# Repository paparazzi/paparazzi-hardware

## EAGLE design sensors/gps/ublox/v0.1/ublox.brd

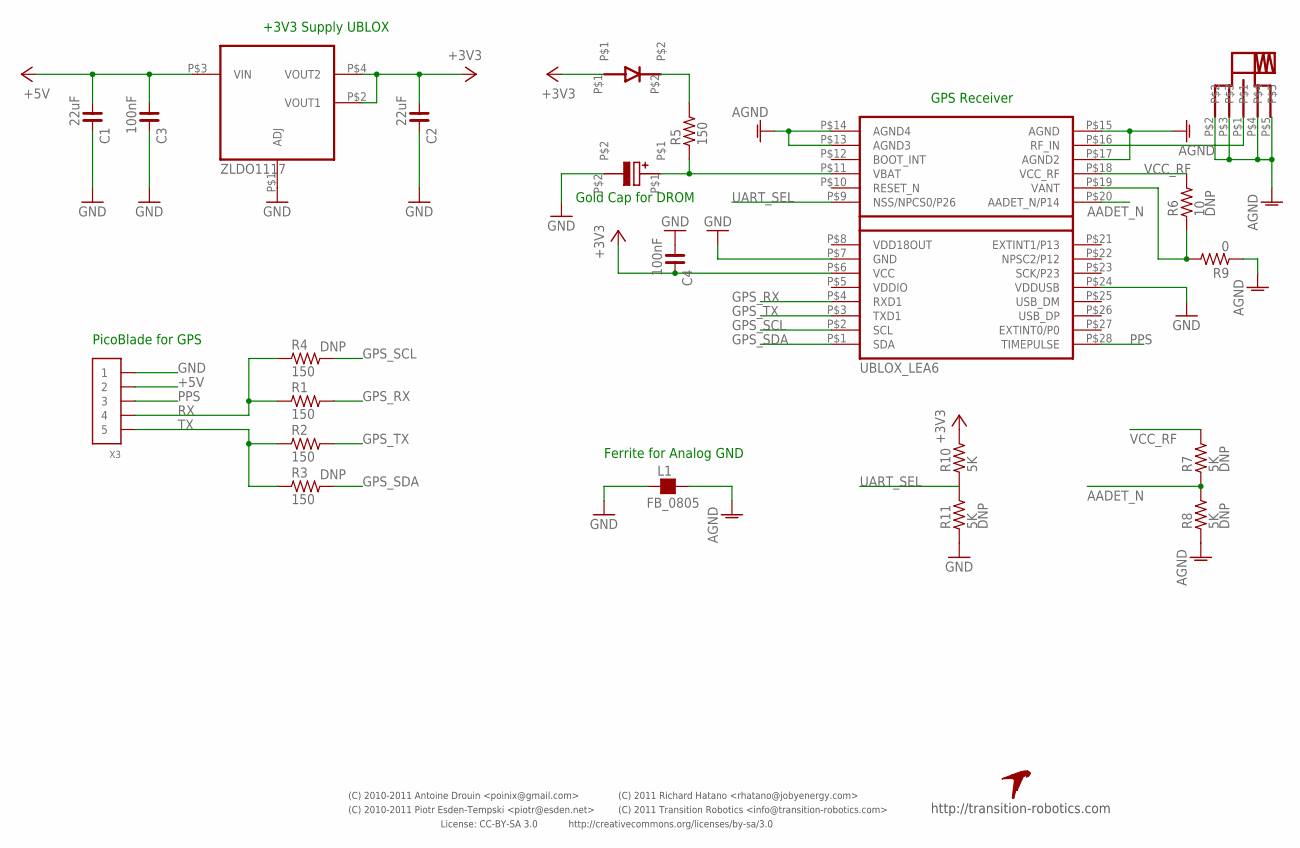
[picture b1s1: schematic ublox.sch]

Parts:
C1, C2: 22uF; C0805
C3, C4: 100nF; C0805
C5: EECEN0F204AK
D1: SOD123
J1: SMA
L1: FB_0805; L0805
R1, R2, R3, R4, R5: 150; R0603
R6: 10; R0603
R7, R8, R10, R11: 5K; R0603
R9: 0; R0603
U1: ZLDO1117
U2: UBLOX_LEA6
U$1: TR-LOGO; PARTNO *
X3: CONN_5-1-53261; PB-53261-05

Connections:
+3V3: C2.1, C4.2, D1.P$1, R10.2, U1.P$2 (VOUT1), U1.P$4 (VOUT2), U2.P$6 (VCC)
+5V: C1.1, C3.1, U1.P$3 (VIN), X3.2
AADET_N: R7.1, R8.2, U2.P$20 (AADET_N/P14)
AGND: J1.P$2, J1.P$3, J1.P$4, J1.P$5, L1.2, R8.1, R9.1, U2.P$13 (AGND3), U2.P$14 (AGND4), U2.P$15 (AGND), U2.P$17 (AGND2)
GND: C1.2, C2.2, C3.2, C4.1, C5.P$2, L1.1, R11.1, U1.P$1 (ADJ), U2.P$7 (GND), U2.P$24 (VDDUSB), X3.1
GPS_RX: R1.2, U2.P$4 (RXD1)
GPS_SCL: R4.2, U2.P$2 (SCL)
GPS_SDA: R3.2, U2.P$1 (SDA)
GPS_TX: R2.2, U2.P$3 (TXD1)
unnamed: R10.1, R11.2
unnamed: D1.P$2, R5.2
unnamed: C5.P$1, R5.1, U2.P$11 (VBAT)
unnamed: J1.P$1, U2.P$16 (RF_IN)
unnamed: R6.1, R9.2, U2.P$19 (VANT)
PPS: U2.P$28 (TIMEPULSE), X3.3
RX: R1.1, R4.1, X3.4
TX: R2.1, R3.1, X3.5
UART_SEL: U2.P$9 (NSS/NPCS0/P26)
VCC_RF: R6.2, R7.2, U2.P$18 (VCC_RF)

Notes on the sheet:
Ferrite for Analog GND
GPS Receiver
PicoBlade for GPS
+3V3 Supply UBLOX
Gold Cap for DROM
License: CC-BY-SA 3.0
http://creativecommons.org/licenses/by-sa/3.0
(C) 2010-2011 Piotr Esden-Tempski <piotr@esden.net>
(C) 2010-2011 Antoine Drouin <poinix@gmail.com>
(C) 2011 Richard Hatano <rhatano@jobyenergy.com>
http://transition-robotics.com
(C) 2011 Transition Robotics <info@transition-robotics.com>

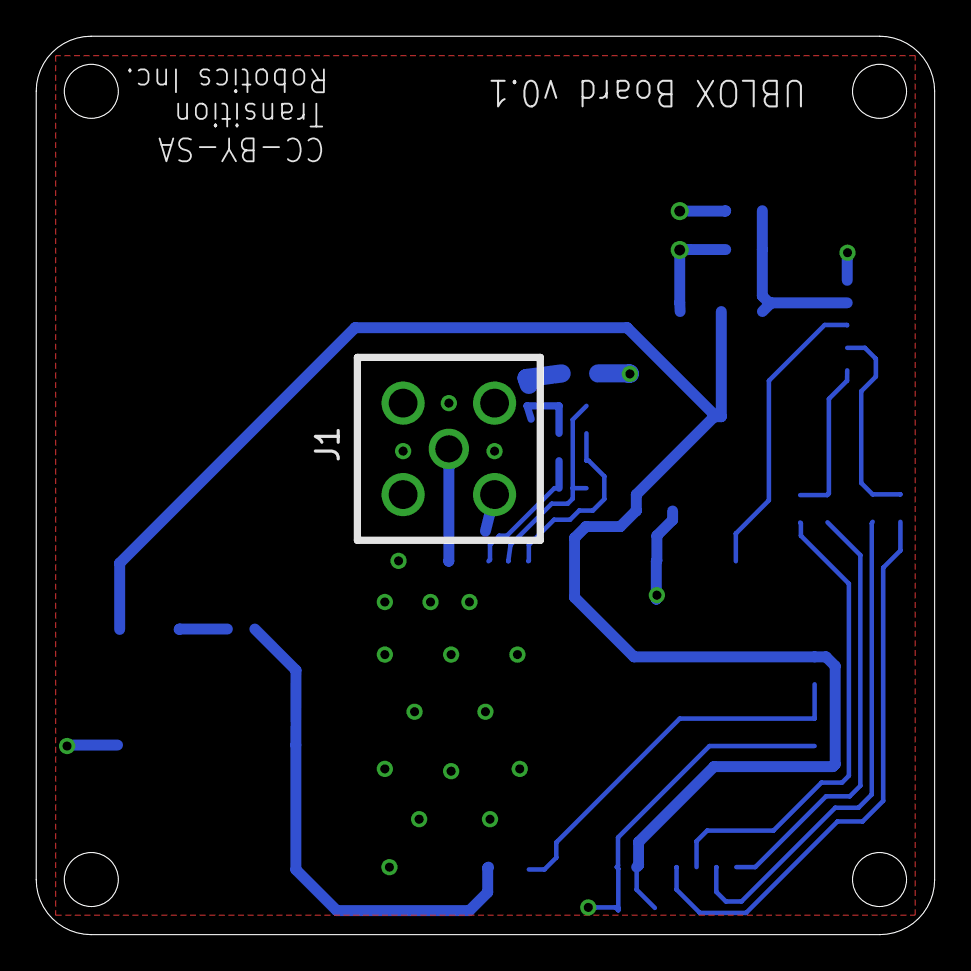
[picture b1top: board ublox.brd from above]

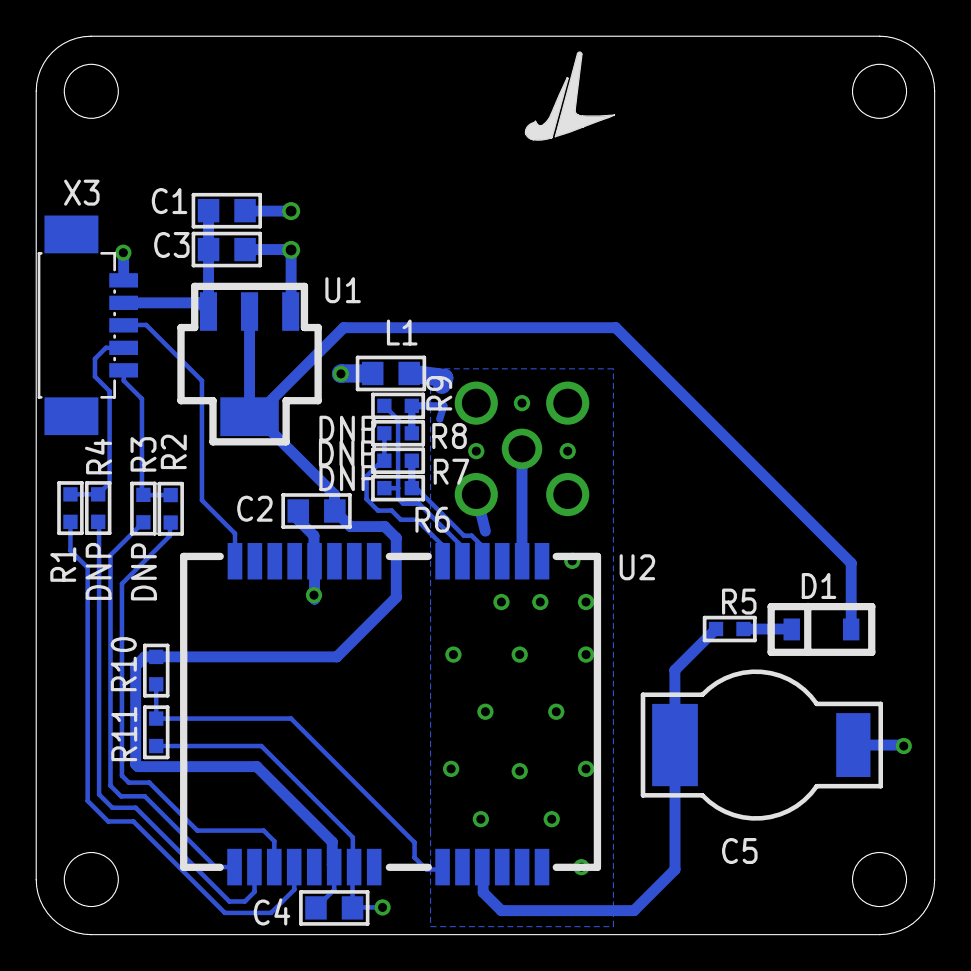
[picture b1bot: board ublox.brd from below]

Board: 4 copper layers, 49.9 x 49.9 mm, 23 parts (22 on the bottom side), 18 nets.

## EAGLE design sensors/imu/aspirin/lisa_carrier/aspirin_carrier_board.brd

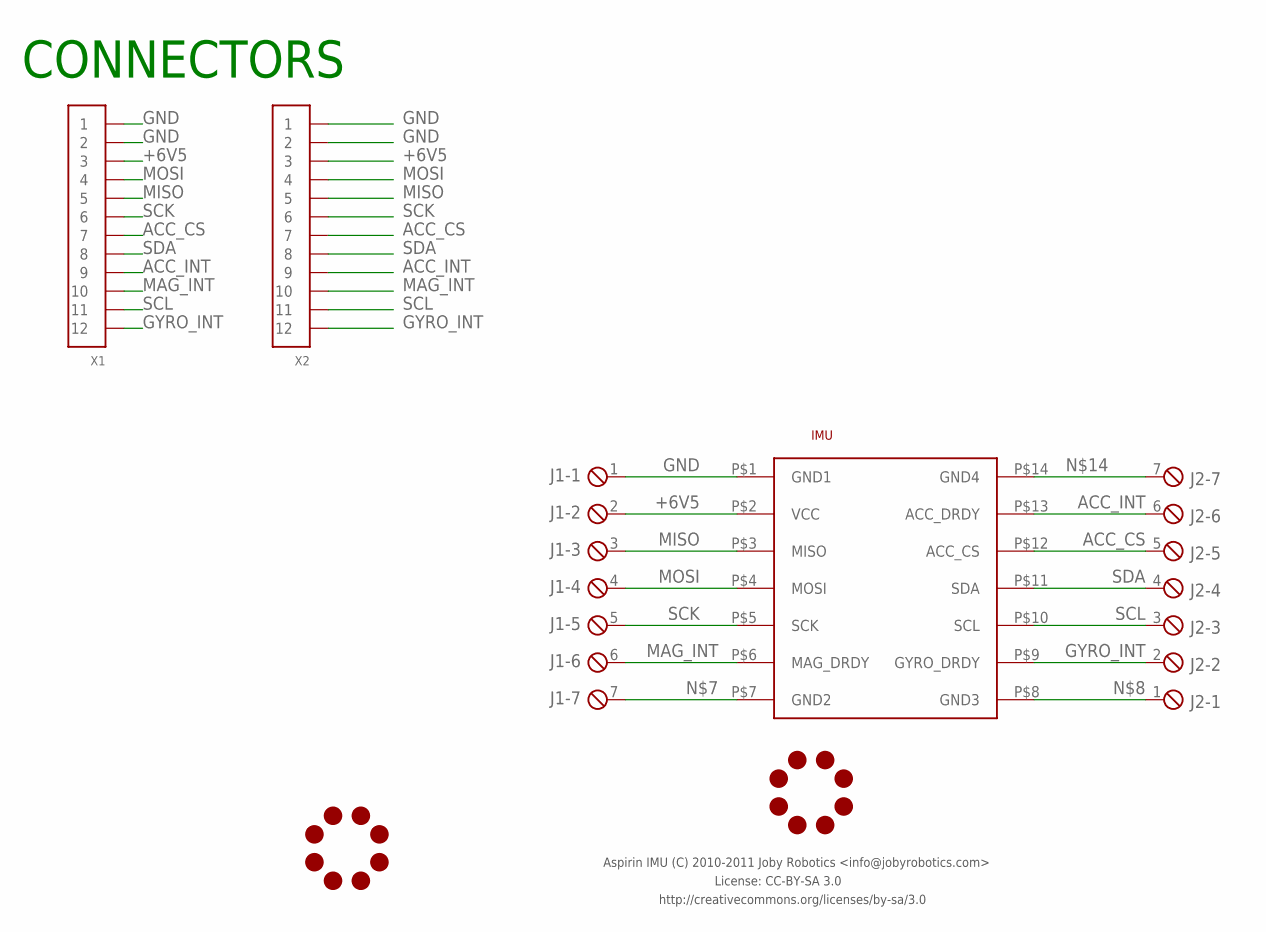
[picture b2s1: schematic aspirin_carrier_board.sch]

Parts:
IMU: ASPIRIN; ASPIRIN_1
J1, J2: MPT7; 7POL254
JL1, JL2: JOBY_LOGO-6MIL; JOBY_LOGO_6MIL
X1: CONN_12-1-53047; PB-53047-12
X2: CONN_12-1-53261; PB-53261-12

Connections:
+6V5: IMU.P$2 (VCC), J1.2, X1.3, X2.3
ACC_CS: IMU.P$12 (ACC_CS), J2.5, X1.7, X2.7
ACC_INT: IMU.P$13 (ACC_DRDY), J2.6, X1.9, X2.9
GND: IMU.P$1 (GND1), J1.1, X1.1, X1.2, X2.1, X2.2
GYRO_INT: IMU.P$9 (GYRO_DRDY), J2.2, X1.12, X2.12
MAG_INT: IMU.P$6 (MAG_DRDY), J1.6, X1.10, X2.10
MISO: IMU.P$3 (MISO), J1.3, X1.5, X2.5
MOSI: IMU.P$4 (MOSI), J1.4, X1.4, X2.4
unnamed: IMU.P$7 (GND2), J1.7
unnamed: IMU.P$8 (GND3), J2.1
unnamed: IMU.P$14 (GND4), J2.7
SCK: IMU.P$5 (SCK), J1.5, X1.6, X2.6
SCL: IMU.P$10 (SCL), J2.3, X1.11, X2.11
SDA: IMU.P$11 (SDA), J2.4, X1.8, X2.8

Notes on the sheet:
CONNECTORS
License: CC-BY-SA 3.0
http://creativecommons.org/licenses/by-sa/3.0
Aspirin IMU (C) 2010-2011 Joby Robotics <info@jobyrobotics.com>

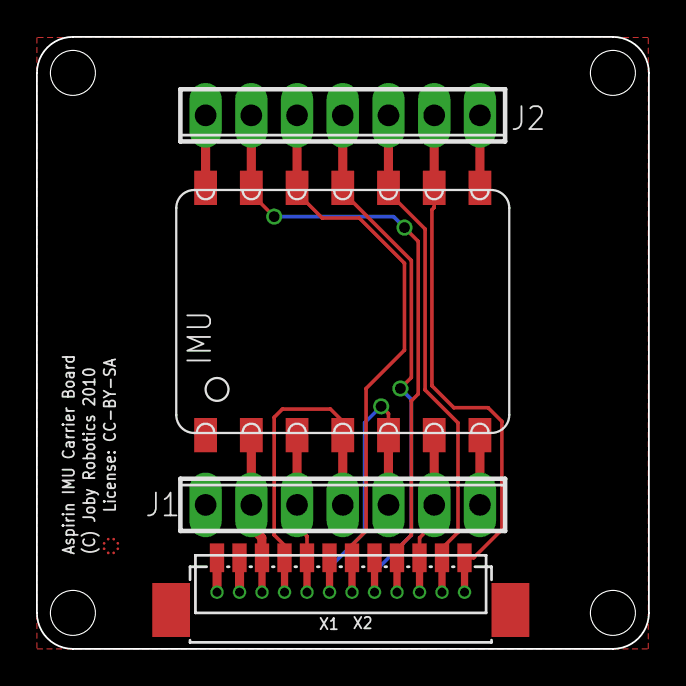
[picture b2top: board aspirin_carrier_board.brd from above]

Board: 4 copper layers, 34.0 x 34.0 mm, 7 parts (1 on the bottom side), 14 nets.

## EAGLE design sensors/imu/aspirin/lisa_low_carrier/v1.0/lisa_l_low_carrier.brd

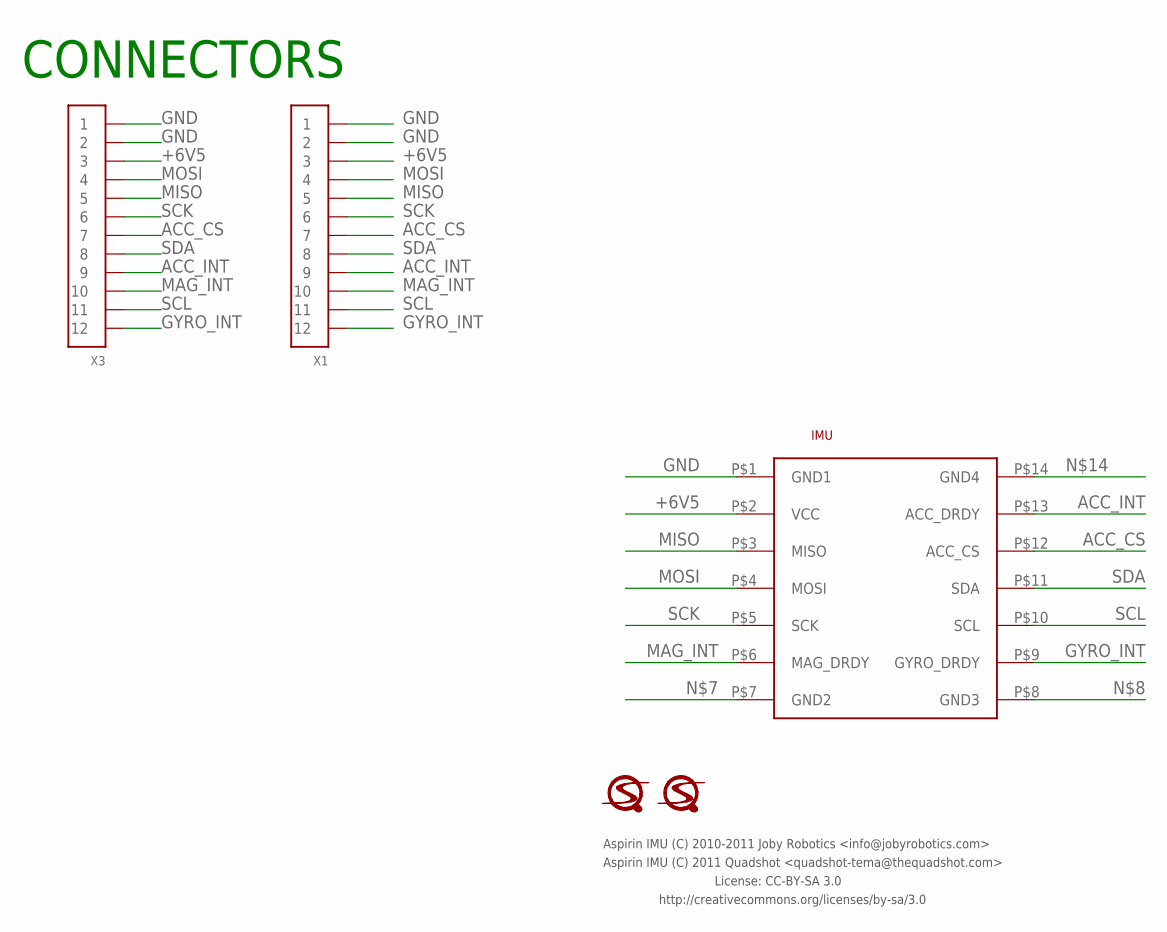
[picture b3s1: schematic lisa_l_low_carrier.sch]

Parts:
IMU: ASPIRIN; ASPIRIN_1
U$1, U$2: LOGO
X1: CONN_12-1-53261; PB-53261-12
X3: CONN_12-1-53047; PB-53047-12

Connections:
+6V5: IMU.P$2 (VCC), X1.3, X3.3
ACC_CS: IMU.P$12 (ACC_CS), X1.7, X3.7
ACC_INT: IMU.P$13 (ACC_DRDY), X1.9, X3.9
GND: IMU.P$1 (GND1), X1.1, X1.2, X3.1, X3.2
GYRO_INT: IMU.P$9 (GYRO_DRDY), X1.12, X3.12
MAG_INT: IMU.P$6 (MAG_DRDY), X1.10, X3.10
MISO: IMU.P$3 (MISO), X1.5, X3.5
MOSI: IMU.P$4 (MOSI), X1.4, X3.4
SCK: IMU.P$5 (SCK), X1.6, X3.6
SCL: IMU.P$10 (SCL), X1.11, X3.11
SDA: IMU.P$11 (SDA), X1.8, X3.8

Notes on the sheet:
CONNECTORS
License: CC-BY-SA 3.0
http://creativecommons.org/licenses/by-sa/3.0
Aspirin IMU (C) 2011 Quadshot <quadshot-tema@thequadshot.com>
Aspirin IMU (C) 2010-2011 Joby Robotics <info@jobyrobotics.com>

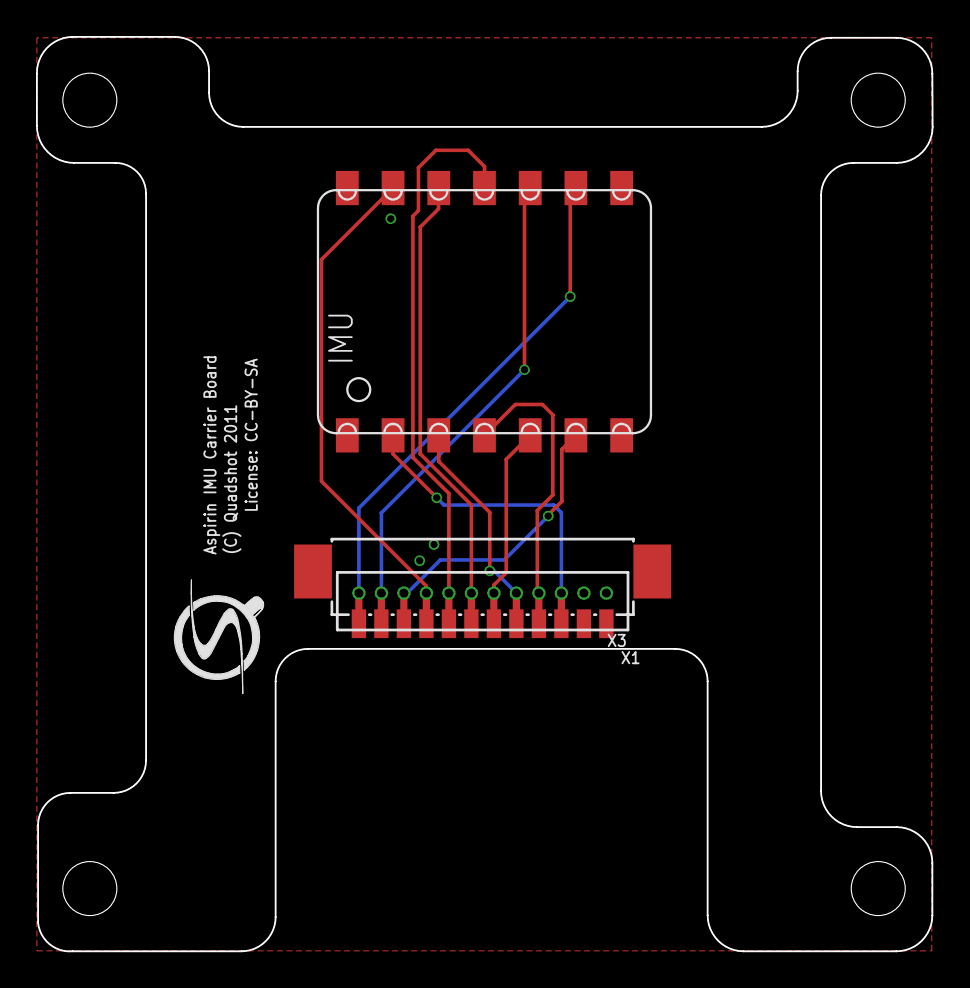
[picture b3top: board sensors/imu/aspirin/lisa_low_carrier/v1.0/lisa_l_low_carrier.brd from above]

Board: 2 copper layers, 49.8 x 50.8 mm, 5 parts (1 on the bottom side), 11 nets.

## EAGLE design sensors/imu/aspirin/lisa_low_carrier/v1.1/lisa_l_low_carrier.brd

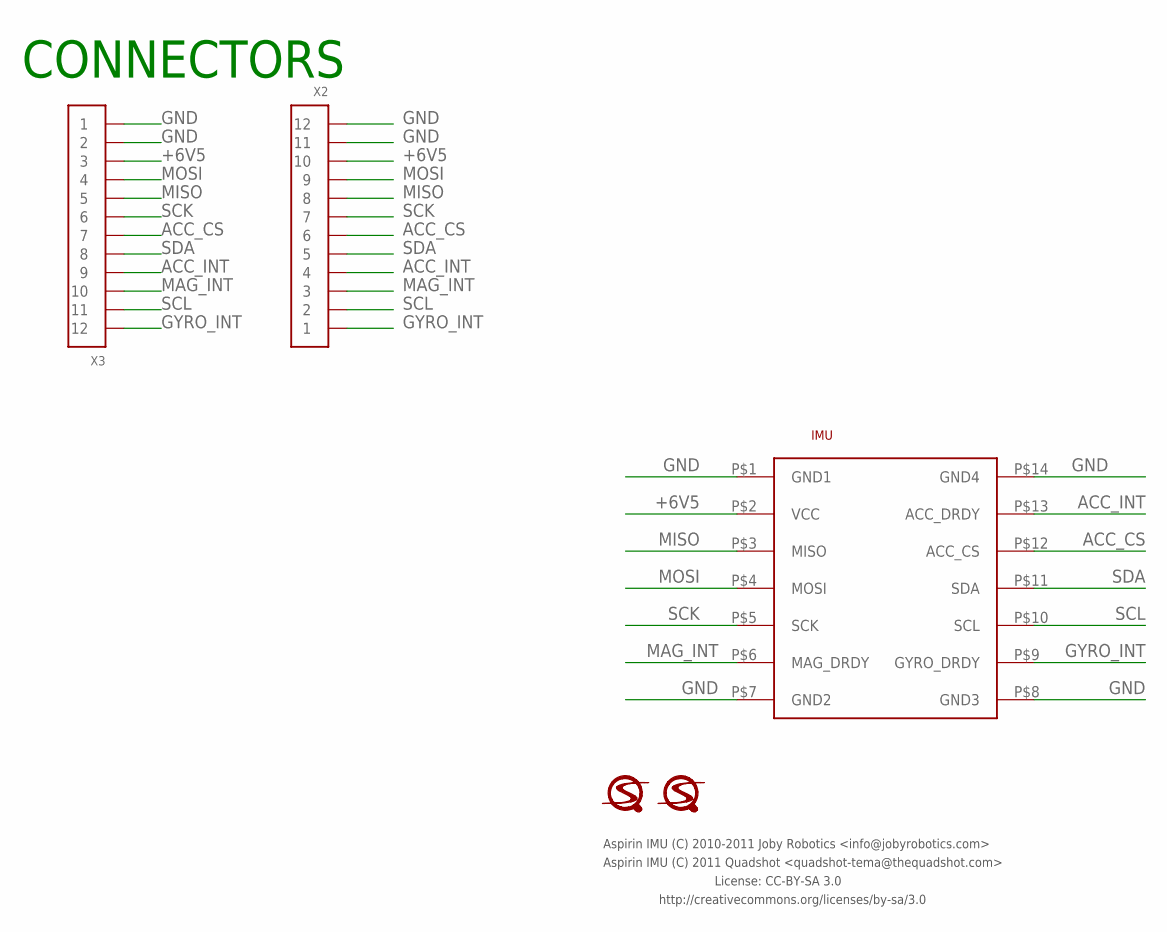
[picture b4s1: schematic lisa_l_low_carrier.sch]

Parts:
IMU: ASPIRIN; ASPIRIN_1
U$1, U$2: LOGO
X2: CONN_12-1-53261; PB-53261-12
X3: CONN_12-1-53047; PB-53047-12

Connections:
+6V5: IMU.P$2 (VCC), X2.10, X3.3
ACC_CS: IMU.P$12 (ACC_CS), X2.6, X3.7
ACC_INT: IMU.P$13 (ACC_DRDY), X2.4, X3.9
GND: IMU.P$1 (GND1), IMU.P$7 (GND2), IMU.P$8 (GND3), IMU.P$14 (GND4), X2.11, X2.12, X3.1, X3.2
GYRO_INT: IMU.P$9 (GYRO_DRDY), X2.1, X3.12
MAG_INT: IMU.P$6 (MAG_DRDY), X2.3, X3.10
MISO: IMU.P$3 (MISO), X2.8, X3.5
MOSI: IMU.P$4 (MOSI), X2.9, X3.4
SCK: IMU.P$5 (SCK), X2.7, X3.6
SCL: IMU.P$10 (SCL), X2.2, X3.11
SDA: IMU.P$11 (SDA), X2.5, X3.8

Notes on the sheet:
CONNECTORS
License: CC-BY-SA 3.0
http://creativecommons.org/licenses/by-sa/3.0
Aspirin IMU (C) 2011 Quadshot <quadshot-tema@thequadshot.com>
Aspirin IMU (C) 2010-2011 Joby Robotics <info@jobyrobotics.com>

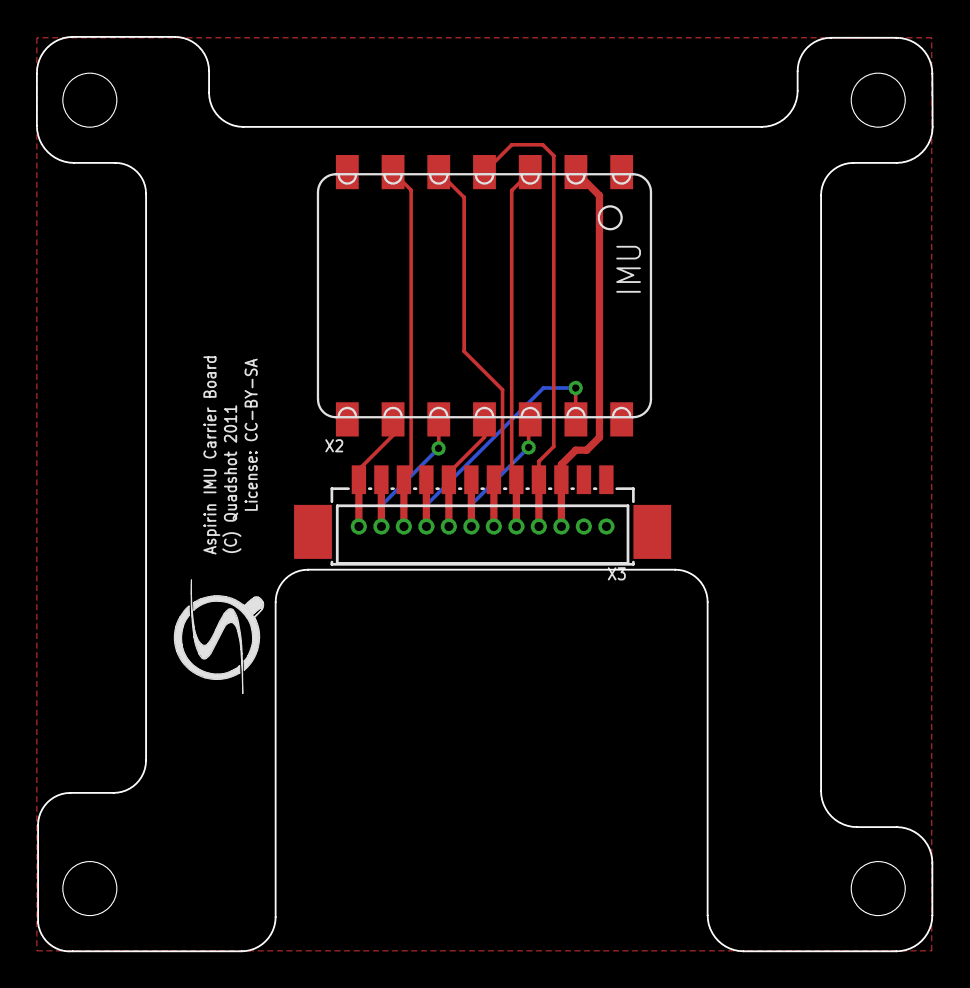
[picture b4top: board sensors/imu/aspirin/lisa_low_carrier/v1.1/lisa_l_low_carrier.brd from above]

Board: 2 copper layers, 49.8 x 50.8 mm, 5 parts (1 on the bottom side), 11 nets.

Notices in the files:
sensors/gps/ublox/v0.1/ublox.brd:
Licensed under:
